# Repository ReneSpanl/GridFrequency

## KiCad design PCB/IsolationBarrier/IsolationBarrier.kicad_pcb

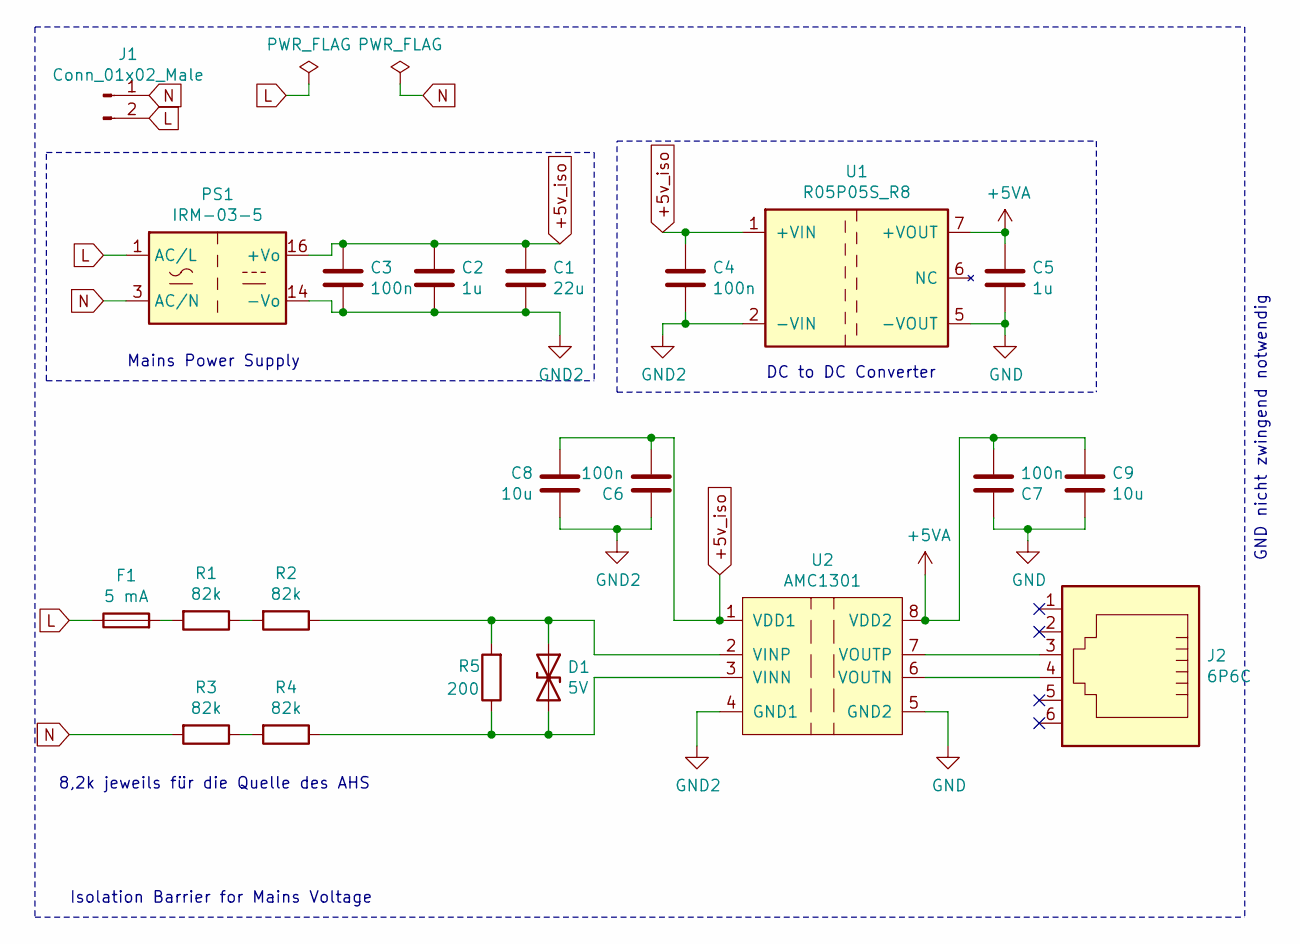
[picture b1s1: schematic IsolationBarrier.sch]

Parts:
C1: 22u; C_1206_3216Metric_Pad1.42x1.75mm_HandSolder
C2, C5: 1u; C_1206_3216Metric_Pad1.42x1.75mm_HandSolder
C3, C4, C6, C7: 100n; C_1206_3216Metric_Pad1.42x1.75mm_HandSolder
C8, C9: 10u; C_1206_3216Metric_Pad1.42x1.75mm_HandSolder
D1: 5V; D_SOD-123
F1: 5 mA; LVR005NS
J1: Conn_01x02_Male; IEC_C8_PCB_Connector
J2: 6P6C
PS1: IRM-03-5; Converter_ACDC_MeanWell_IRM-03-xx_THT
R1, R2, R3, R4: 82k; R_1206_3216Metric_Pad1.42x1.75mm_HandSolder
R5: 200; R_1206_3216Metric_Pad1.42x1.75mm_HandSolder
U1: R05P05S_R8; RECOM-R05P05S
U2: AMC1301; SOIC-8_7.5x5.85mm_P1.27mm

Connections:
+5VA: C5.1, C7.2, C9.1, U1.7 (+VOUT), U2.8 (VDD2)
+5v_iso: C1.1, C2.1, C3.1, C4.1, C6.2, C8.1, PS1.16 (+Vo), U1.1 (+VIN), U2.1 (VDD1)
GND: C5.2, C7.1, C9.2, U1.5 (-VOUT), U2.5 (GND2)
GND2: C1.2, C2.2, C3.2, C4.2, C6.1, C8.2, PS1.14 (-Vo), U1.2 (-VIN), U2.4 (GND1)
L: F1.1, J1.2, PS1.1 (AC/L)
N: J1.1, PS1.3 (AC/N), R3.2
unnamed: D1.1 (A1), R2.1, R5.2, U2.2 (VINP)
unnamed: D1.2 (A2), R4.1, R5.1, U2.3 (VINN)
unnamed: F1.2, R1.2
unnamed: J2.3, U2.7 (VOUTP)
unnamed: J2.4, U2.6 (VOUTN)
unnamed: R1.1, R2.2
unnamed: R3.1, R4.2

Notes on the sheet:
Isolation Barrier for Mains Voltage
Mains Power Supply
GND nicht zwingend notwendig
DC to DC Converter
8,2k jeweils für die Quelle des AHS

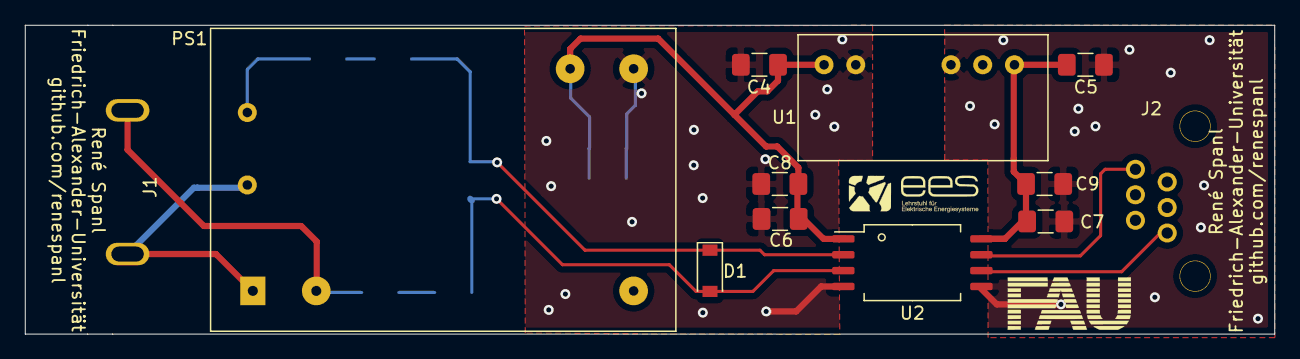
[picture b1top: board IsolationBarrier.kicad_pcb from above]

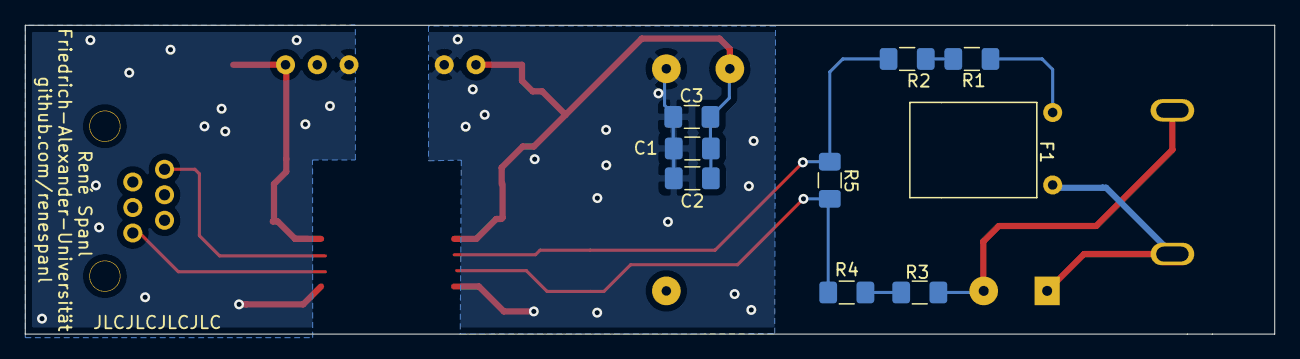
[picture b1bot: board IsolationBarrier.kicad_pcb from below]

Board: 2 copper layers, 100.0 x 24.7 mm, 21 parts (9 on the bottom side), 13 nets.

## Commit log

2021-05-28 First Comment. PCB missing
2021-05-28 Final Commit
